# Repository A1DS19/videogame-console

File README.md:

# RP2350 Videogame Console

A homebrew videogame console built around the Raspberry Pi **RP2350B**, with a matching
8-button arcade controller. Both PCBs are designed circuit-as-code (JITX) and taken through
KiCad layout → Freerouting → DRC → JLCPCB fabrication.

| Console | Controller |
|---|---|
|  |  |

## The console

The main board: an RP2350B microcontroller that reads up to two controllers, renders to a TV
over HDMI/DVI, and plays game audio through a small speaker.

- **MCU:** RP2350B (QFN-80) + 16 MB QSPI flash (W25Q128JV), 12 MHz crystal
- **Video:** HDMI connector driven as DVI over the RP2350 HSTX peripheral (4 TMDS pairs)
- **Power:** USB-C in → 3.3 V buck (TLV62569) + the RP2350 core SMPS
- **Controllers:** 2× JST-XH 1×10 ports (one per controller), each with SRV05-4A ESD
- **Audio:** PWM → RC filter → PAM8302A class-D amp → JST-PH speaker
- **I/O:** BOOTSEL + RUN buttons, status LED
- **Board:** 72 × 66 mm, 4-layer (JLC04161H), 75 parts

## The controller

An 8-button arcade-style gamepad on a single faceplate PCB that plugs into a console port
with a JST-XH cable.

- **Buttons:** 8 tactile switches (active-low; pull-ups + 3V3 live on the console end)
- **Link:** JST-XH 1×10 (8 buttons + GND + 3V3)
- **Protection:** SRV05-4A ESD arrays on the button lines
- **Board:** 120 × 70 mm, 2-layer, 31 parts

## Layout

```
pcbs/
  console/        RP2350 console — JITX source, KiCad export, routed board, fab
    routing/production/   JLCPCB gerbers + drill + CPL + BOM
  controller/     arcade gamepad — JITX source, routed board, fab
    fab/                  JLCPCB gerbers + drill + CPL + BOM + STEP
  screenshots/    3D renders
```

Each board's `routing/` holds the canonical routed `.kicad_pcb`. The JLCPCB upload set
(gerbers zip, drill, CPL/position CSV, and an LCSC-resolved BOM) lives in the console's
`routing/production/` and the controller's `fab/`.

## Manufacturing status

- **Console** — fully routed + **DRC clean** (0 unconnected; only the benign `J1` USB-C shield
  annular). Datasheet-validation fixes applied (81 parts). Fab package in
  `routing/production-v2/` (gerbers + drill + CPL + STEP + JLCPCB-uploadable BOM, gate PASS).
- **Controller** — fully routed, DRC clean, fab package ready.

## Rebuilding from source

Each project is a JITX (Python) design. Recreate its virtualenv in the project folder
(`.venv` is not committed and is path-specific), then build with the project `.venv/bin/jitx`.
The routed boards are committed because they are not regenerable from source (Freerouting +
manual finishing) — do not re-export over them.

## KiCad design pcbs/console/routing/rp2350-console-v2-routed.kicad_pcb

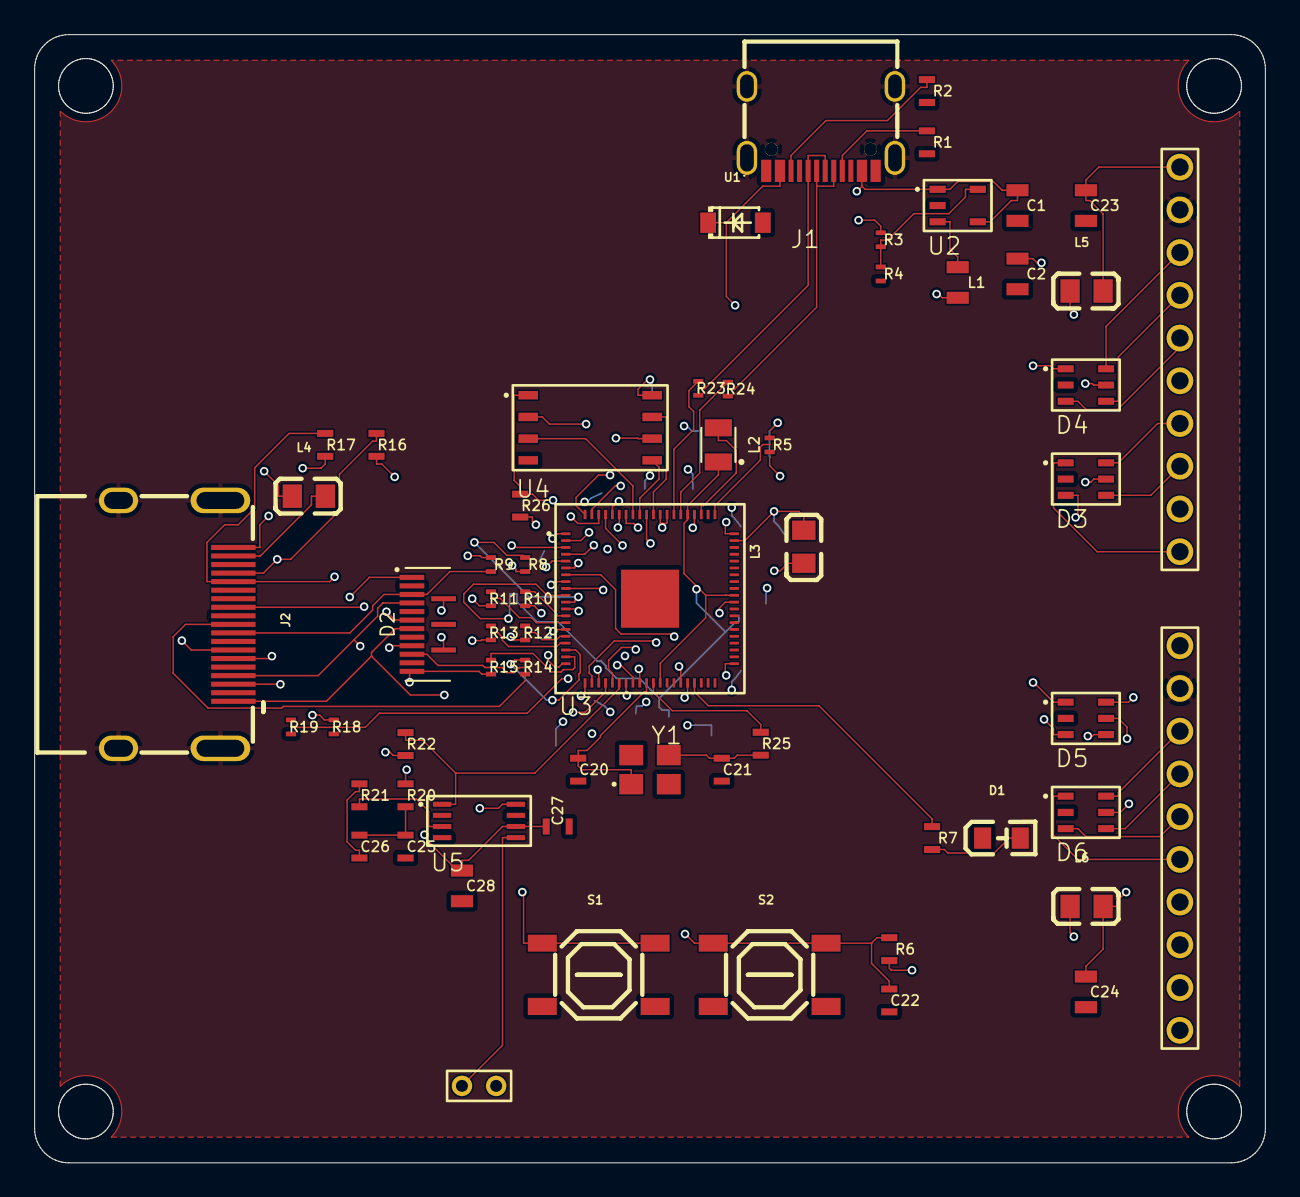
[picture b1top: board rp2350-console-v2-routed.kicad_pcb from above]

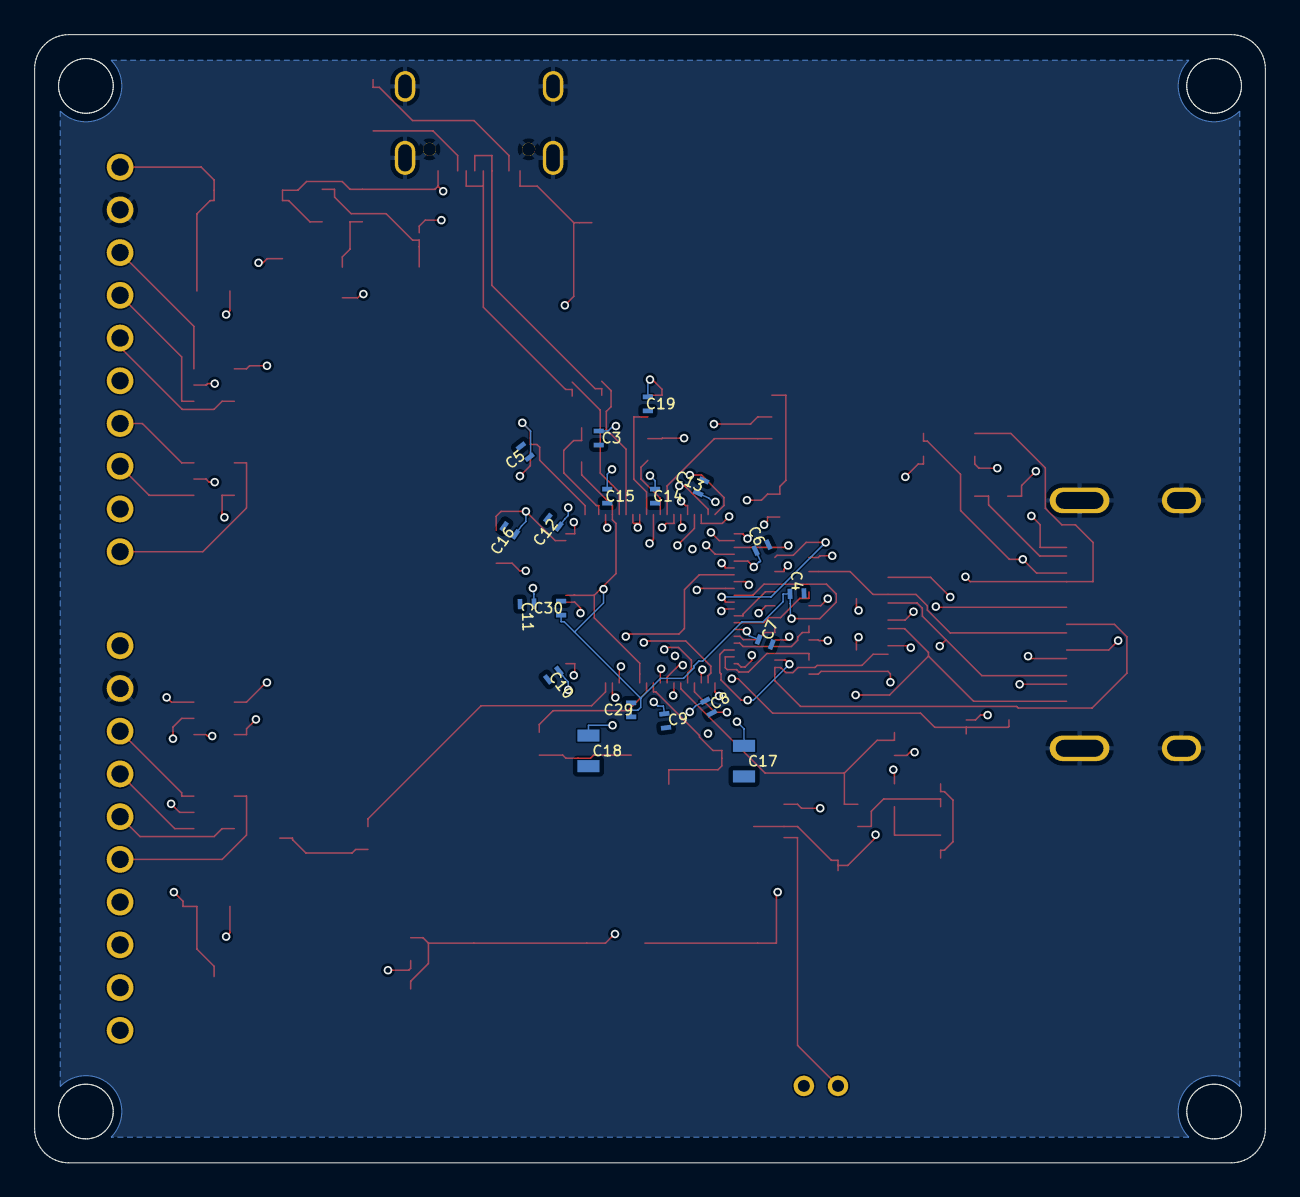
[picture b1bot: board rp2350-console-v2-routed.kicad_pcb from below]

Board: 4 copper layers, 72.0 x 66.0 mm, 81 parts (19 on the bottom side), 74 nets.

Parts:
C1: 10 µF; DBLANDPATTERN_10
C2: 22 µF; DBLANDPATTERN_11
C3: 4.7 µF; DBLANDPATTERN_14
C4: 4.7 µF; DBLANDPATTERN_15
C5: 4.7 µF; DBLANDPATTERN_19
C6: 100 nF; DBLANDPATTERN_20
C7: 100 nF; DBLANDPATTERN_21
C8: 100 nF; DBLANDPATTERN_22
C9: 100 nF; DBLANDPATTERN_23
C10: 100 nF; DBLANDPATTERN_24
C11: 100 nF; DBLANDPATTERN_25
C12: 100 nF; DBLANDPATTERN_26
C13: 100 nF; DBLANDPATTERN_27
C14: 100 nF; DBLANDPATTERN_28
C15: 100 nF; DBLANDPATTERN_29
C16: 100 nF; DBLANDPATTERN_30
C17: 10 µF; DBLANDPATTERN_31
C18: 10 µF; DBLANDPATTERN_32
C19: 100 nF; DBLANDPATTERN_33
C20: 30 pF; DBLANDPATTERN_35
C21: 30 pF; DBLANDPATTERN_36
C22: 100 nF; DBLANDPATTERN_39
C23: 10 µF; DBLANDPATTERN_57
C24: 10 µF; DBLANDPATTERN_58
C25: 2.2 nF; DBLANDPATTERN_60
C26: 1 µF; DBLANDPATTERN_62
C27: 1 µF; DBLANDPATTERN_64
C28: 10 µF; DBLANDPATTERN_65
C29: 100 nF; DBLANDPATTERN_16
C30: 100 nF; DBLANDPATTERN_17
D1: KT-0805G; DBLANDPATTERN_4
D2: TPD8S009DSMR; TPD8S009_COMPOSITE_LANDPATTERN
D3: SRV05-4A; SRV05_4A_COMPOSITE_LANDPATTERN
D4: SRV05-4A; SRV05_4A_COMPOSITE_LANDPATTERN_1
D5: SRV05-4A; SRV05_4A_COMPOSITE_LANDPATTERN_2
D6: SRV05-4A; SRV05_4A_COMPOSITE_LANDPATTERN_3
J1: TYPE-C-31-M-12; Pkg_TYPEC31M12LANDPATTERN
J2: HDMI-001S; DBLANDPATTERN_41
J3: B10B-XH-A(LF)(SN); JSTXH10_COMPOSITE_LANDPATTERN
J4: B10B-XH-A(LF)(SN); JSTXH10_COMPOSITE_LANDPATTERN_1
J5: B2B-PH-K-S(LF)(SN); JSTPH2_COMPOSITE_LANDPATTERN
L1: 2.2 µH; DBLANDPATTERN_1
L2: AOTA-B201610S3R3-101-T; AOTAB201610S3R3_COMPOSITE_LANDPATTERN
L3: GZ2012D101TF; DBLANDPATTERN_5
L4: GZ2012D601TF; DBLANDPATTERN_42
L5: GZ2012D601TF; DBLANDPATTERN_55
L6: GZ2012D601TF; DBLANDPATTERN_56
R1: 5.1 kΩ; DBLANDPATTERN_6
R2: 5.1 kΩ; DBLANDPATTERN_7
R3: 51.7 kΩ; DBLANDPATTERN_12
R4: 11.5 kΩ; DBLANDPATTERN_13
R5: 33 Ω; DBLANDPATTERN_18
R6: 10 kΩ; DBLANDPATTERN_38
R7: 1 kΩ; DBLANDPATTERN_40
R8: 0 Ω; DBLANDPATTERN_43
R9: 0 Ω; DBLANDPATTERN_44
R10: 0 Ω; DBLANDPATTERN_45
R11: 0 Ω; DBLANDPATTERN_46
R12: 0 Ω; DBLANDPATTERN_47
R13: 0 Ω; DBLANDPATTERN_48
R14: 0 Ω; DBLANDPATTERN_49
R15: 0 Ω; DBLANDPATTERN_50
R16: 4.7 kΩ; DBLANDPATTERN_51
R17: 4.7 kΩ; DBLANDPATTERN_52
R18: 110 kΩ; DBLANDPATTERN_53
R19: 165 kΩ; DBLANDPATTERN_54
R20: 3.3 kΩ; DBLANDPATTERN_59
R21: 0 Ω; DBLANDPATTERN_61
R22: 100 kΩ; DBLANDPATTERN_63
R23: 27 Ω; DBLANDPATTERN_8
R24: 27 Ω; DBLANDPATTERN_9
R25: 1 kΩ; DBLANDPATTERN_34
R26: 1 kΩ; DBLANDPATTERN_37
S1: TS-1187A-B-A-B; DBLANDPATTERN_2
S2: TS-1187A-B-A-B; DBLANDPATTERN_3
U1: SMF5.0A; DBLANDPATTERN
U2: TLV62569DBVR; TLV62569_COMPOSITE_LANDPATTERN
U3: RP2350B; RP2350B_COMPOSITE_LANDPATTERN
U4: W25Q128JVSIQ; W25Q128JV_COMPOSITE_LANDPATTERN
U5: PAM8302AASCR; PAM8302A_COMPOSITE_LANDPATTERN
Y1: X322512MSB4SI; CRYSTAL12MHZ_COMPOSITE_LANDPATTERN

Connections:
A: R26.2, S1.1, S1.2
ADC_AVDD: C16.1, L3.2, U3.landpattern_p59
AMP_SD: R22.1, U3.landpattern_p26, U5.landpattern_p1
D0_N: D2.landpattern_p3, J2.9, R9.2
D0_P: D2.landpattern_p1, J2.7, R8.2
D1_N: D2.landpattern_p6, J2.6, R11.2
D1_P: D2.landpattern_p4, J2.4, R10.2
D2_N: D2.landpattern_p9, J2.3, R13.2
D2_P: D2.landpattern_p7, J2.1, R12.2
D3_N: D2.landpattern_p12, J2.12, R15.2
D3_P: D2.landpattern_p10, J2.10, R14.2
DVDD: C4.1, C29.1, C30.1, L2.landpattern_p1, U3.landpattern_p10, U3.landpattern_p32, U3.landpattern_p51, U3.landpattern_p65
FB: R3.2, R4.1, U2.landpattern_p5
GND: C1.2, C2.2, C3.2, C4.2, C5.2, C6.2, C7.2, C8.2, C9.2, C10.2, C11.2, C12.2, C13.2, C14.2, C15.2, C16.2, C17.2, C18.2, C19.2, C20.2, C21.2, C22.2, C23.2, C24.2, C25.2, C27.2, C28.2, C29.2, C30.2, D1.1, D2.landpattern_p2, D2.landpattern_p5, D2.landpattern_p8, D2.landpattern_p11, D3.landpattern_p2, D4.landpattern_p2, D5.landpattern_p2, D6.landpattern_p2, J1.9, J1.10, J1.13, J1.14, J1.15, J1.16, J1.17, J1.18, J2.2, J2.5, J2.8, J2.11, J2.17, J2.20, J2.21, J2.22, J2.23, J3.landpattern_p9, J4.landpattern_p9, R1.2, R2.2, R4.2, R19.2, S1.3, S1.4, S2.3, S2.4, U1.2, U2.landpattern_p2, U3.landpattern_p62, U3.landpattern_thermal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, U4.landpattern_p4, U5.landpattern_p4, U5.landpattern_p7, Y1.landpattern_p2, Y1.landpattern_p4
GPIO[0]: D3.landpattern_p1, J3.landpattern_p1, U3.landpattern_p77
GPIO[1]: D3.landpattern_p3, J3.landpattern_p2, U3.landpattern_p78
GPIO[2]: D3.landpattern_p4, J3.landpattern_p3, U3.landpattern_p79
GPIO[3]: D3.landpattern_p6, J3.landpattern_p4, U3.landpattern_p80
GPIO[4]: D4.landpattern_p1, J3.landpattern_p5, U3.landpattern_p1
GPIO[5]: D4.landpattern_p3, J3.landpattern_p6, U3.landpattern_p2
GPIO[6]: D4.landpattern_p4, J3.landpattern_p7, U3.landpattern_p3
GPIO[7]: D4.landpattern_p6, J3.landpattern_p8, U3.landpattern_p4
GPIO[8]: D5.landpattern_p1, J4.landpattern_p1, U3.landpattern_p6
GPIO[9]: D5.landpattern_p3, J4.landpattern_p2, U3.landpattern_p7
GPIO[10]: D5.landpattern_p4, J4.landpattern_p3, U3.landpattern_p8
GPIO[11]: D5.landpattern_p6, J4.landpattern_p4, U3.landpattern_p9
GPIO[12]: R8.1, U3.landpattern_p11
GPIO[13]: R9.1, U3.landpattern_p12
GPIO[14]: R10.1, U3.landpattern_p13
GPIO[15]: R11.1, U3.landpattern_p14
GPIO[16]: R12.1, U3.landpattern_p16
GPIO[17]: R13.1, U3.landpattern_p17
GPIO[18]: R14.1, U3.landpattern_p18
GPIO[19]: R15.1, U3.landpattern_p19
GPIO[20]: D6.landpattern_p1, J4.landpattern_p5, U3.landpattern_p20
GPIO[21]: D6.landpattern_p3, J4.landpattern_p6, U3.landpattern_p21
GPIO[22]: D6.landpattern_p4, J4.landpattern_p7, U3.landpattern_p22
GPIO[23]: D6.landpattern_p6, J4.landpattern_p8, U3.landpattern_p23
GPIO[24]: R20.1, U3.landpattern_p25
GPIO[26]: J2.16, R16.1, U3.landpattern_p27
GPIO[27]: J2.15, R17.1, U3.landpattern_p28
GPIO[28]: R18.2, R19.1, U3.landpattern_p36
GPIO[29]: R7.1, U3.landpattern_p37
INP: R21.2, U5.landpattern_p3
LED_A: D1.2, R7.2
OUTN: J5.landpattern_p2, U5.landpattern_p8
OUTP: J5.landpattern_p1, U5.landpattern_p5
QSPI_SCLK: U3.landpattern_p71, U4.landpattern_p6
QSPI_SD0: U3.landpattern_p72, U4.landpattern_p5
QSPI_SD1: U3.landpattern_p74, U4.landpattern_p2
QSPI_SD2: U3.landpattern_p73, U4.landpattern_p3
QSPI_SD3: U3.landpattern_p70, U4.landpattern_p7
QSPI_SS: R26.1, U3.landpattern_p75, U4.landpattern_p1
RUN: C22.1, R6.1, S2.1, S2.2, U3.landpattern_p35
SW: L1.1, U2.landpattern_p3
USB_DM: R24.1, U3.landpattern_p66
USB_DP: R23.1, U3.landpattern_p67
V3V3: C2.1, C3.1, C6.1, C7.1, C8.1, C9.1, C10.1, C11.1, C12.1, C13.1, C14.1, C15.1, C17.1, C18.1, C19.1, D2.landpattern_p13, D2.landpattern_p15, D3.landpattern_p5, D4.landpattern_p5, D5.landpattern_p5, D6.landpattern_p5, L1.2, L3.1, L5.1, L6.1, R3.1, R5.2, R6.2, R16.2, R17.2, R22.2, U3.landpattern_p5, U3.landpattern_p15, U3.landpattern_p24, U3.landpattern_p29, U3.landpattern_p41, U3.landpattern_p50, U3.landpattern_p60, U3.landpattern_p64, U3.landpattern_p68, U3.landpattern_p69, U3.landpattern_p76, U4.landpattern_p8
VBUS: C1.1, C27.1, C28.1, J1.11, J1.12, L4.1, U1.1, U2.landpattern_p1, U2.landpattern_p4, U5.landpattern_p6
VREG_AVDD: C5.1, R5.1, U3.landpattern_p61
VREG_LX: L2.landpattern_p2, U3.landpattern_p63
XIN: C20.1, U3.landpattern_p30, Y1.landpattern_p1
XOUT: R25.1, U3.landpattern_p31
c_ac_p1: C25.1, C26.1, R20.2
c_port_bulk[0]_p1: C23.1, J3.landpattern_p10, L5.2
c_port_bulk[1]_p1: C24.1, J4.landpattern_p10, L6.2
p1: J1.2, R1.1
p2: C26.2, R21.1
p[2]: J2.18, L4.2
r_cc2_p1: J1.8, R2.1
r_hi_p1: J2.19, R18.1
r_usb_dm_p2: J1.3, J1.5, R24.2
r_usb_dp_p2: J1.4, J1.6, R23.2
xtal_XOUT: C21.1, R25.2, Y1.landpattern_p3

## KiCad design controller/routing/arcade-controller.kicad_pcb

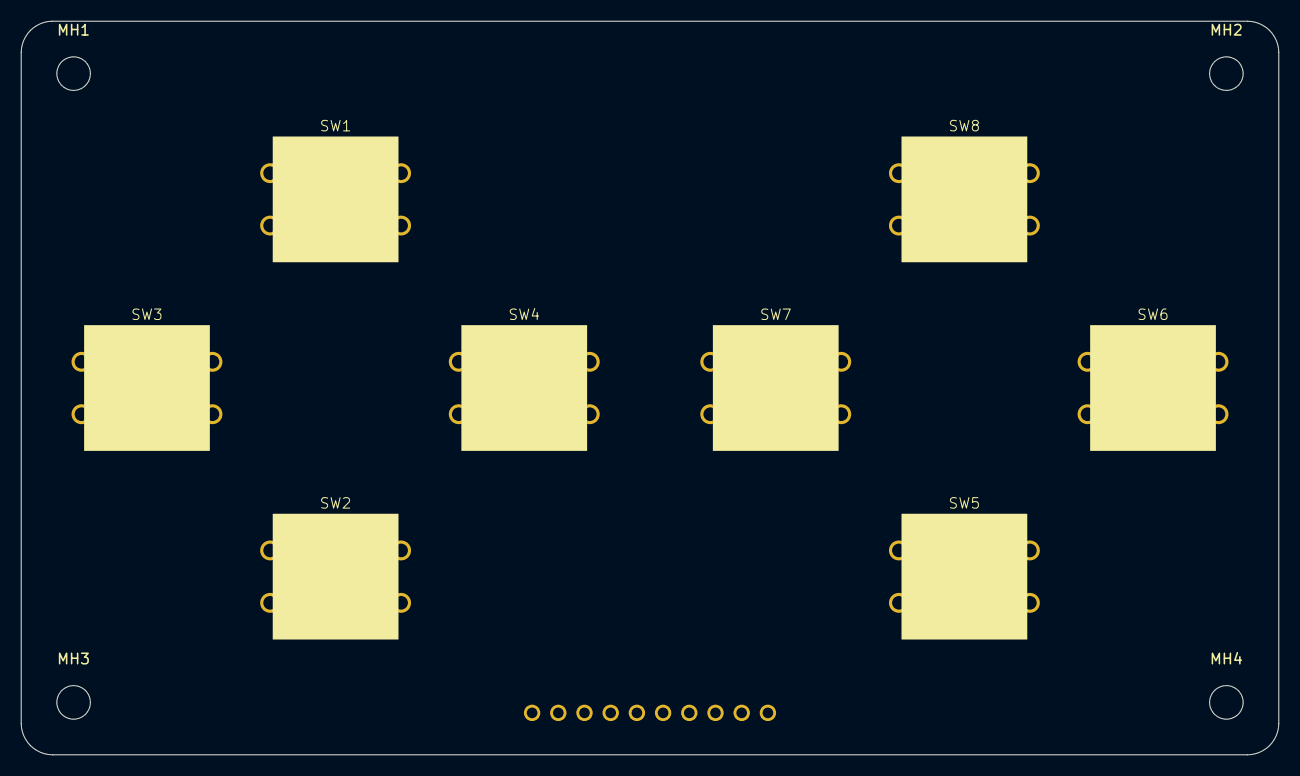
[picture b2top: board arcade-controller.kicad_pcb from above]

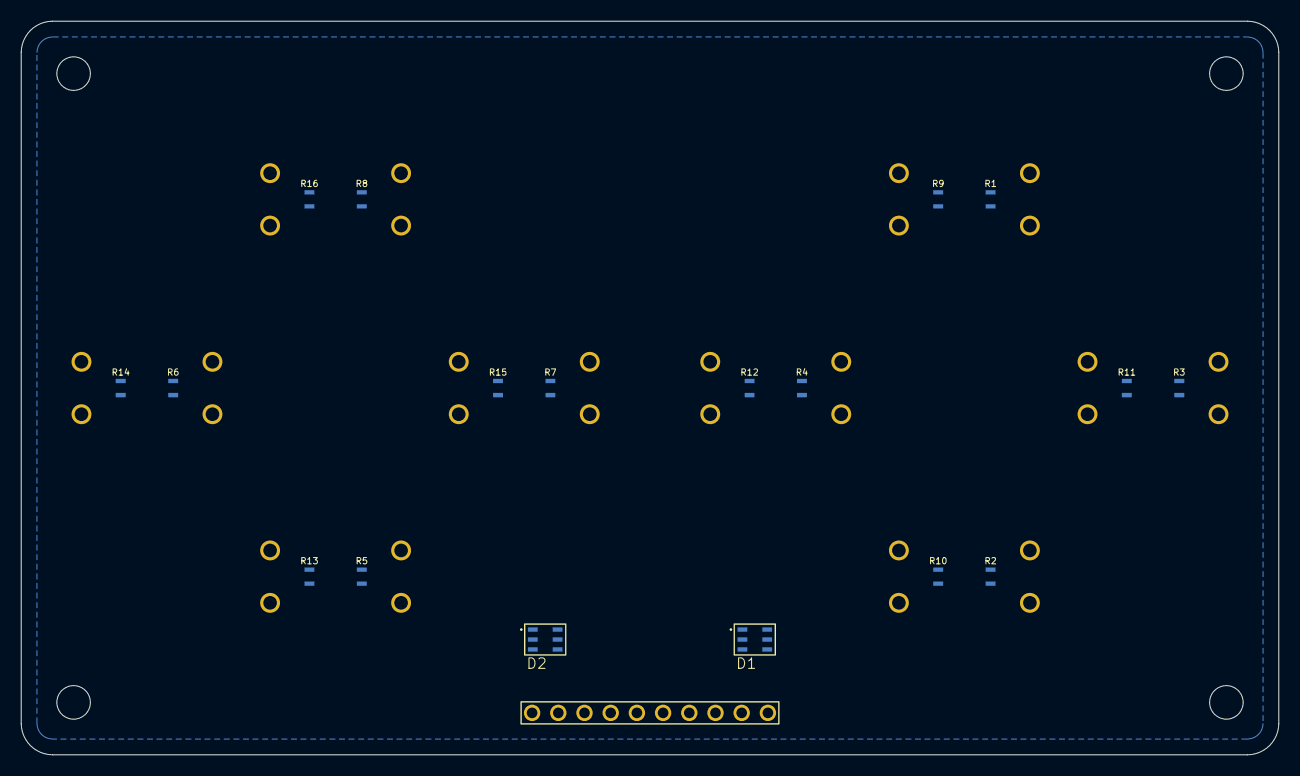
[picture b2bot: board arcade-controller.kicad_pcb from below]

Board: 2 copper layers, 120.0 x 70.0 mm, 31 parts (19 on the bottom side), 18 nets, no tracks yet.

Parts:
D1: SRV05-4A; SRV05_4A_COMPOSITE_LANDPATTERN
D2: SRV05-4A; SRV05_4A_COMPOSITE_LANDPATTERN_1
J1: B10B-XH-A(LF)(SN); JSTXH10_COMPOSITE_LANDPATTERN
MH1, MH2, MH3, MH4: MountingHole_3.2mm_M3
R1: 10 kΩ; DBLANDPATTERN
R2: 10 kΩ; DBLANDPATTERN_1
R3: 10 kΩ; DBLANDPATTERN_2
R4: 10 kΩ; DBLANDPATTERN_3
R5: 10 kΩ; DBLANDPATTERN_4
R6: 10 kΩ; DBLANDPATTERN_5
R7: 10 kΩ; DBLANDPATTERN_6
R8: 10 kΩ; DBLANDPATTERN_7
R9: 220 Ω; DBLANDPATTERN_8
R10: 220 Ω; DBLANDPATTERN_9
R11: 220 Ω; DBLANDPATTERN_10
R12: 220 Ω; DBLANDPATTERN_11
R13: 220 Ω; DBLANDPATTERN_12
R14: 220 Ω; DBLANDPATTERN_13
R15: 220 Ω; DBLANDPATTERN_14
R16: 220 Ω; DBLANDPATTERN_15
SW1, SW2, SW3, SW4, SW5, SW6, SW7, SW8: K2-1103DP-Q4SW-04; Pkg_TACTILEBUTTONLANDPATTERN

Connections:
BTN0_INT: R1.2, R9.1, SW1.1, SW1.2
BTN0_OUT: D1.landpattern_p1, J1.landpattern_p1, R9.2
BTN1_INT: R2.2, R10.1, SW2.1, SW2.2
BTN1_OUT: D1.landpattern_p3, J1.landpattern_p2, R10.2
BTN2_INT: R3.2, R11.1, SW3.1, SW3.2
BTN2_OUT: D1.landpattern_p4, J1.landpattern_p3, R11.2
BTN3_INT: R4.2, R12.1, SW4.1, SW4.2
BTN3_OUT: D1.landpattern_p6, J1.landpattern_p4, R12.2
BTN4_INT: R5.2, R13.1, SW5.1, SW5.2
BTN4_OUT: D2.landpattern_p1, J1.landpattern_p5, R13.2
BTN5_INT: R6.2, R14.1, SW6.1, SW6.2
BTN5_OUT: D2.landpattern_p3, J1.landpattern_p6, R14.2
BTN6_INT: R7.2, R15.1, SW7.1, SW7.2
BTN6_OUT: D2.landpattern_p4, J1.landpattern_p7, R15.2
BTN7_INT: R8.2, R16.1, SW8.1, SW8.2
BTN7_OUT: D2.landpattern_p6, J1.landpattern_p8, R16.2
GND: D1.landpattern_p2, D2.landpattern_p2, J1.landpattern_p9, SW1.3, SW1.4, SW2.3, SW2.4, SW3.3, SW3.4, SW4.3, SW4.4, SW5.3, SW5.4, SW6.3, SW6.4, SW7.3, SW7.4, SW8.3, SW8.4
V3V3: D1.landpattern_p5, D2.landpattern_p5, J1.landpattern_p10, R1.1, R2.1, R3.1, R4.1, R5.1, R6.1, R7.1, R8.1

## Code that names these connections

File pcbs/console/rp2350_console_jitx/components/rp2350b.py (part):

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  • GPIO40–GPIO47 carry the 8 ADC inputs (ADC0–ADC7) on QFN-80 (Table 1119).
  • GPIO0–GPIO47 (48 pins) is the full bank used for the 2 controller ports,
    PWM audio, status LED, and DDC/HPD — exposed here as the GPIO[0..47] list.
  • QSPI_SS (pin 75) doubles as the USB BOOTSEL strap (Table 1428).
  • GND has no dedicated pin — it is the central exposed pad only (Table 1432).
"""

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        for i, pad in enumerate(_IOVDD_PADS):
            mapping[self.IOVDD[i]] = [lp.p[pad]]
        for i, pad in enumerate(_DVDD_PADS):
            mapping[self.DVDD[i]] = [lp.p[pad]]
        mapping[self.ADC_AVDD] = [lp.p[59]]
        mapping[self.VREG_AVDD] = [lp.p[61]]
        mapping[self.VREG_PGND] = [lp.p[62]]
        mapping[self.VREG_LX] = [lp.p[63]]
        mapping[self.VREG_VIN] = [lp.p[64]]
        mapping[self.VREG_FB] = [lp.p[65]]
        mapping[self.USB_DM] = [lp.p[66]]
        mapping[self.USB_DP] = [lp.p[67]]
        mapping[self.USB_OTP_VDD] = [lp.p[68]]
        mapping[self.QSPI_IOVDD] = [lp.p[69]]
        mapping[self.QSPI_SD3] = [lp.p[70]]
        mapping[self.QSPI_SCLK] = [lp.p[71]]
        mapping[self.QSPI_SD0] = [lp.p[72]]
        mapping[self.QSPI_SD2] = [lp.p[73]]
        mapping[self.QSPI_SD1] = [lp.p[74]]
        mapping[self.QSPI_SS] = [lp.p[75]]
        mapping[self.XIN] = [lp.p[30]]
        mapping[self.XOUT] = [lp.p[31]]
        mapping[self.SWCLK] = [lp.p[33]]
        mapping[self.SWDIO] = [lp.p[34]]
        mapping[self.RUN] = [lp.p[35]]
        mapping[self.GND] = [lp.thermal_pads[0]]

        self.mappings = [PadMapping(mapping)]
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
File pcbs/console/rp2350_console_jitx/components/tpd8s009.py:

"""
Texas Instruments TPD8S009DSMR — 8-channel TVS/ESD protection array for
DisplayPort/HDMI/DVI TMDS lines.  LCSC C471873.

Package: DSM (R-PDSO-N15), 15-pin SON, body 6.50 x 2.50 mm
  (datasheet "Package Information" table, p.1: SON(15), 2.50 x 6.50 mm body).

Pinout — datasheet p.3, "Figure 4-1. DSM Package 15-Pin SON Top View" +
"Pin Functions" table:
  Pin  1  D0+   ESD port   (TMDS data 0, +)
  Pin  2  GND   ground
  Pin  3  D0-   ESD port   (TMDS data 0, -)
  Pin  4  D1+   ESD port   (TMDS data 1, +)
  Pin  5  GND   ground
  Pin  6  D1-   ESD port   (TMDS data 1, -)
  Pin  7  D2+   ESD port   (TMDS data 2, +)
  Pin  8  GND   ground
  Pin  9  D2-   ESD port   (TMDS data 2, -)
  Pin 10  D3+   ESD port   (TMDS data 3/clock, +)
  Pin 11  GND   ground
  Pin 12  D3-   ESD port   (TMDS data 3/clock, -)
  Pin 13  VCC   I/O supply
  Pin 14  N.C.  not internally connected
  Pin 15  VCC   I/O supply

Each ESD channel is a single SHUNT node (steering diodes clamp the line to
GND/VCC per the "Simplified Internal Schematic", p.1) — it is NOT a series
pass-through; the "Easy Straight-Through Routing Package" feature is a layout
convenience (pins arranged so the TMDS pairs route straight past with short
stubs), not separate connector-side/MCU-side terminals.

Landpattern — datasheet p.16 "LAND PATTERN" (drawing 4210120/A) + p.15
"MECHANICAL DATA" (DSM R-PDSO-N15, 4208854/A):
  Row A (pins 1-12): one long edge, pitch 0.50 mm, span 5.50 mm.
  Row B (pins 13-15): opposite long edge, pitch 1.50 mm, span 3.00 mm.
  Recommended copper land: 0.30 mm (across) x 1.45 mm (along), non-solder-mask
  defined (0.06 mm mask relief all around), stencil aperture 0.25 x 1.40 mm.
  Row-to-row land centre-to-centre = 3.30 mm overall - 1.45 mm land = 1.85 mm
  => each row centred at Y = +-0.925 mm.
Pad centres cross-checked against the JITX parts-DB landpattern for
TPD8S009DSMR (build --no-dependency-check probe) — identical poses.
No exposed/thermal pad (lead-frame SON, terminals on two opposing edges only).

3D model: manufacturer STEP from the JITX parts DB (resolved via
Part(mpn="TPD8S009DSMR")), vendored to models/TPD8S009DSMR.stp.
"""

import jitx
from jitx import PadMapping
from jitx.anchor import Anchor
from jitx.feature import Courtyard, Custom, Paste, Silkscreen, Soldermask
from jitx.landpattern import Landpattern, Pad
from jitx.model3d import Model3D
from jitx.net import Port
from jitx.shapes.composites import rectangle
from jitx.shapes.primitive import Circle, Polyline, Text
from jitxlib.symbols.box import BoxSymbol, Column, PinGroup, Row


# ======================================================================
# Pad — single SMD land shared by all 15 terminals (datasheet p.16)
# ======================================================================


class _Land(Pad):
    """SMD land 0.30 (across) x 1.45 mm (along), NSMD + stencil aperture."""

    shape = rectangle(0.30, 1.45)
    soldermask = Soldermask(rectangle(0.42, 1.57))  # +0.06 mm relief all around
    paste = Paste(rectangle(0.25, 1.40))  # datasheet stencil aperture


# ======================================================================
# Landpattern (module scope — JITX prohibits subclassing inside __init__)
# ======================================================================


class _Tpd8s009Landpattern(Landpattern):
    """
    R-PDSO-N15 (DSM) land pattern, top (PCB) view.

    Row A (Y = +0.925): pins 1-12 left-to-right at X = +2.75 .. -2.75, 0.50 pitch.
    Row B (Y = -0.925): pins 13/14/15 at X = -1.50 / 0.00 / +1.50, 1.50 pitch.
    Pin 1 (D0+) sits at the +X end of row A (top view).
    """

    name = "TI:R-PDSO-N15_TPD8S009DSM"

    # Row A — pins 1..12 at Y = +0.925, X stepping -0.50 from +2.75.
    # Row B — pins 13..15 at Y = -0.925.
    p = {
        1: _Land().at(2.75, 0.925),
        2: _Land().at(2.25, 0.925),
        3: _Land().at(1.75, 0.925),
        4: _Land().at(1.25, 0.925),
        5: _Land().at(0.75, 0.925),
        6: _Land().at(0.25, 0.925),
        7: _Land().at(-0.25, 0.925),
        8: _Land().at(-0.75, 0.925),
        9: _Land().at(-1.25, 0.925),
        10: _Land().at(-1.75, 0.925),
        11: _Land().at(-2.25, 0.925),
        12: _Land().at(-2.75, 0.925),
        13: _Land().at(-1.50, -0.925),
        14: _Land().at(0.00, -0.925),
        15: _Land().at(1.50, -0.925),
    }

    # Silkscreen: short body-edge lines (clear of the lands) + pin-1 dot.
    # Body 6.60 x 2.60 mm => half-extents X = 3.30, Y = 1.30 (datasheet p.15).
    silkscreen = [
        Silkscreen(Polyline(0.12, [(3.30, -1.30), (3.30, 1.30)])),
        Silkscreen(Polyline(0.12, [(-3.30, -1.30), (-3.30, 1.30)])),
        Silkscreen(Circle(radius=0.15).at((3.20, 1.80))),  # pin-1 marker
    ]
    reference_designator = Silkscreen(Text(">REF", 0.8, Anchor.C).at((0.0, 2.35)))
    value_label = Custom(Text(">VALUE", 0.8, Anchor.C).at((0.0, -2.35)), name="Fab")

    # Courtyard covers the lands (Y +-1.65) and body (X +-3.30) + ~0.25 mm.
    courtyard = Courtyard(rectangle(7.10, 3.80))


# ======================================================================
# Component
# ======================================================================


class Tpd8s009(jitx.Component):
    """TI TPD8S009 8-channel HDMI/DisplayPort TMDS ESD protection array, SON-15."""

    mpn = "TPD8S009DSMR"
    manufacturer = "Texas Instruments"
    lcsc = "C471873"
    reference_designator_prefix = "D"
    datasheet = "https://www.ti.com/lit/ds/symlink/tpd8s009.pdf"

    # 8 high-speed ESD channels = the 4 TMDS differential pairs (pins 1,3,4,6,7,9,10,12)
    D0_P = Port()  # pin 1
    D0_N = Port()  # pin 3
    D1_P = Port()  # pin 4
    D1_N = Port()  # pin 6
    D2_P = Port()  # pin 7
    D2_N = Port()  # pin 9
    D3_P = Port()  # pin 10
    D3_N = Port()  # pin 12

    # Ground returns — pins 2, 5, 8, 11
    GND = [Port() for _ in range(4)]

    # I/O supply rail — pins 13, 15
    VCC = [Port() for _ in range(2)]

    # Not internally connected — pin 14
    NC = Port()

    landpattern = _Tpd8s009Landpattern()

    # Manufacturer STEP (JITX parts DB), vendored to models/.
    # Resolves relative to this file: components/ -> project_root/models/.
    # Origin-centred DB model (position/rotation = 0); HUMAN: confirm seating
    # in the 3D view after export and adjust if needed.
    model3ds = [Model3D("../../models/TPD8S009DSMR.stp")]

    def __init__(self) -> None:
        # Symbol: TMDS channels on the left (pair-ordered), VCC/NC right, GND down.
        self.symbol = BoxSymbol(
            rows=Row(
                left=PinGroup(
                    self.D0_P,
                    self.D0_N,
                    self.D1_P,
                    self.D1_N,
                    self.D2_P,
                    self.D2_N,
                    self.D3_P,
                    self.D3_N,
                ),
                right=PinGroup(*self.VCC, self.NC),
            ),
            columns=Column(
                down=PinGroup(*self.GND),
            ),
        )

        # Port -> pad number per datasheet "Pin Functions" table (p.3).
        lp = self.landpattern
        self.mappings = [
            PadMapping(
                {
                    self.D0_P: lp.p[1],
                    self.GND[0]: lp.p[2],
                    self.D0_N: lp.p[3],
                    self.D1_P: lp.p[4],
                    self.GND[1]: lp.p[5],
                    self.D1_N: lp.p[6],
                    self.D2_P: lp.p[7],
                    self.GND[2]: lp.p[8],
                    self.D2_N: lp.p[9],
                    self.D3_P: lp.p[10],
                    self.GND[3]: lp.p[11],
                    self.D3_N: lp.p[12],
                    self.VCC[0]: lp.p[13],
                    self.NC: lp.p[14],
                    self.VCC[1]: lp.p[15],
                }
            )
        ]


Device: type[Tpd8s009] = Tpd8s009

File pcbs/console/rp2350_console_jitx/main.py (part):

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        # so this insert is plain (the inductor is the switch-node element, not a
        # decoupling cap) — see grep-gate disposition.
        self.l_buck.insert(self.buck.SW, self.V3V3)
        # Output cap pinned across the inductor output (l_buck.p2 = V3V3) and the
        # buck ground return — both Ports, so short_trace keeps it at the output.
        self.c_buck_out = Capacitor(capacitance=22e-6, case="0805")
        self.c_buck_out.insert(self.l_buck.p2, self.buck.GND, short_trace=True)
        # FB divider from constraints (NEVER hand-picked): V3V3 -> FB -> GND.
        # TLV62569 VFB = 0.6 V nominal (datasheet "Feedback regulation voltage":
        # 0.588 / 0.600 / 0.612 V = 0.6 V +/-2%), so v_out = 0.6 V +/-2%.
        self.fb_div = voltage_divider_from_constraints(
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            + self.mcu.DVDD[2]
            + self.mcu.VREG_FB,
        ]
        # C6 (4.7 uF) core-reg input decoupling; C7 (4.7 uF) on DVDD; both pinned.
        self.c6_core_in = Capacitor(capacitance=4.7e-6, case="0402")
        self.c6_core_in.insert(self.mcu.VREG_VIN, self.mcu.VREG_PGND, short_trace=True)
        self.c7_core_out = Capacitor(capacitance=4.7e-6, case="0402")
        self.c7_core_out.insert(self.mcu.DVDD[0], self.mcu.GND, short_trace=True)
        # 2x 100 nF on the inner DVDD pads (DVDD[1]=pad32, DVDD[2]=pad51) close to the
        # pins per datasheet §6.1.3 (C7 4.7 uF above sits on the furthest DVDD pad).
        self.c_dvdd = [Capacitor(capacitance=100e-9, case="0402") for _ in range(2)]
        self.c_dvdd[0].insert(self.mcu.DVDD[1], self.mcu.GND, short_trace=True)
        self.c_dvdd[1].insert(self.mcu.DVDD[2], self.mcu.GND, short_trace=True)
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            self.mcu.QSPI_SD3 + self.flash.IO3_HOLD,
        ]

        # --- 12 MHz crystal + 1k XOUT damping + load caps ---
        # R2 (1k) in series with XOUT: REQUIRED at 3.3 V IOVDD to keep the crystal from
        # being over-driven/damaged (RP2350 HW guide §4 Fig 10). The load cap stays on
        # the crystal side of R2.
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        # --- Status LED on GPIO29 (lit when the GPIO is driven high) ---
        self.LED_A = Net(name="LED_A")  # series-resistor / LED-anode node
        self.r_led = Resistor(resistance=1e3, case="0603")
        self.r_led.insert(self.mcu.GPIO[29], self.LED_A)
        self.led_nets = [
            self.LED_A + self.led_status.A,
            self.GND + self.led_status.K,
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            self.VBUS + self.fb_hdmi5v.p[1],
            self.hdmi.V5 + self.fb_hdmi5v.p[2],
        ]
        # DDC I2C: SDA=GPIO26, SCL=GPIO27, with 4.7 k pull-ups to V3V3.
        self.ddc_nets = [
            self.mcu.GPIO[26] + self.hdmi.SDA,
            self.mcu.GPIO[27] + self.hdmi.SCL,
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            self.r_in.p2 + self.amp.INP,  # gain resistor -> IN+
            self.GND + self.amp.INN,  # single-ended input reference
        ]
        # Amp shutdown (active-low): driven by GPIO25, 100 k pull-up to V3V3
        # -> default HIGH = amp ENABLED at boot (firmware mutes by driving low).
        self.SD = Net(name="AMP_SD")
        self.SD += self.amp.SD + self.mcu.GPIO[25]
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
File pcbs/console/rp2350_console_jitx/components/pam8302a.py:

"""
Diodes PAM8302AASCR — 2.5 W filterless Class-D mono audio amplifier, MSOP-8.

LCSC C113367. Drives the console's 8 Ω speaker (via a JST-PH port).

Pinout (datasheet DS41333 Rev.6 page 1, "Pin Assignments" MSOP-8 Top View) —
verified against the JITX parts-DB pin_properties for C113367:
  Pin 1: SD    (shutdown, ACTIVE-LOW: logic-low = amp off; overbar /SD)
  Pin 2: NC    (no internal connection)
  Pin 3: IN+   (non-inverting audio input)        -> port INP
  Pin 4: IN-   (inverting audio input)            -> port INN
  Pin 5: VO+   (bridge-tied speaker output +)     -> port OUTP
  Pin 6: VDD   (2.0-5.5 V supply)
  Pin 7: GND   (ground)
  Pin 8: VO-   (bridge-tied speaker output -)     -> port OUTN

MSOP-8 mechanical (datasheet page 10, "Package Outline Dimensions", all mm):
  D  (body length):     2.90-3.10
  E1 (body width):      2.90-3.10
  E  (lead span):       4.70-5.10
  e  (pitch):           0.65
  L  (lead foot length):0.40-0.80
  b  (lead width):      0.22-0.38
  A  (overall height):  max 1.10  (A2 body 0.75-0.95)

Closed-loop gain is set externally (datasheet page 7): GV = 20*log(150k/(10k+Rin)) dB
(~23.5 dB max at Rin=0; the old "2x(142k/Rin)" shorthand is wrong — it diverges at
Rin=0). The differential output is filterless and must
NOT be AC-coupled or ground-referenced; route VO+/VO- straight to the speaker.
"""

import jitx
from jitx import PadMapping
from jitx.model3d import Model3D
from jitx.net import Port
from jitx.toleranced import Toleranced
from jitxlib.landpatterns.generators.sop import SOP, SOPLead
from jitxlib.landpatterns.leads import LeadProfile
from jitxlib.landpatterns.package import RectanglePackage
from jitxlib.symbols.box import BoxSymbol, Column, PinGroup, Row


class PAM8302A(jitx.Component):
    """2.5 W Class-D mono audio amplifier, MSOP-8 (Diodes PAM8302AASCR)."""

    mpn = "PAM8302AASCR"
    manufacturer = "Diodes Incorporated"
    lcsc = "C113367"
    reference_designator_prefix = "U"
    datasheet = "https://www.diodes.com/assets/Datasheets/PAM8302A.pdf"

    # Ports — one per physical pin, named per datasheet page-1 Pin Assignments.
    SD = Port()  # pin 1 — shutdown, active-low (low = amp off)
    NC = Port()  # pin 2 — no connection
    INP = Port()  # pin 3 — IN+ non-inverting input
    INN = Port()  # pin 4 — IN- inverting input
    OUTP = Port()  # pin 5 — VO+ speaker output (+)
    VDD = Port()  # pin 6 — supply 2.0-5.5 V
    GND = Port()  # pin 7 — ground
    OUTN = Port()  # pin 8 — VO- speaker output (-)

    # MSOP-8 landpattern via the SOP generator (gull-wing, 0.65 mm pitch).
    # Dimensions are the datasheet page-10 mechanical drawing (see module docstring).
    landpattern = (
        SOP(num_leads=8)
        .lead_profile(
            LeadProfile(
                span=Toleranced.min_max(4.70, 5.10),  # E — lead tip-to-tip
                pitch=0.65,  # e
                type=SOPLead(
                    length=Toleranced.min_max(0.40, 0.80),  # L — foot length
                    width=Toleranced.min_max(0.22, 0.38),  # b — lead width
                ),
            )
        )
        .package_body(
            RectanglePackage(
                width=Toleranced.min_max(2.90, 3.10),  # E1 — body width
                length=Toleranced.min_max(2.90, 3.10),  # D — body length
                height=Toleranced.min_max(0.86, 1.10),  # A2..A
            )
        )
    )

    # BoxSymbol: inputs + shutdown on the left, speaker outputs on the right,
    # VDD up / GND down — mirrors the datasheet pin directions.
    symbol = BoxSymbol(
        rows=Row(
            left=PinGroup(SD, NC, INP, INN),
            right=PinGroup(OUTP, OUTN),
        ),
        columns=Column(
            up=PinGroup(VDD),
            down=PinGroup(GND),
        ),
    )

    # 3D model: the exact PAM8302AASCR (LCSC C113367) STEP from the JITX parts DB,
    # auto-downloaded to 3d-models/ during the DB probe and copied to models/ with a
    # clean name. The generator landpattern carries no DB 3D automatically, so attach
    # it here to complete the board STEP export. Resolves relative to this file:
    # components/ -> project_root/models/.
    # The DB tags this model "unknown transformation coordinates - please validate
    # before use" (HUMAN: confirm seating in the 3D view after export; adjust
    # offset/rotation if it does not sit flat on the MSOP-8 footprint).
    model3ds = [Model3D("../../models/PAM8302AASCR.stp")]

    # Explicit PadMapping — SOP LinearNumbering pads p[1]..p[8] map to the
    # datasheet pin numbers (left col 1-4 top->bottom, right col 5-8 bottom->top).
    def __init__(self) -> None:
        lp = self.landpattern
        self.mappings = [
            PadMapping(
                {
                    self.SD: [lp.p[1]],
                    self.NC: [lp.p[2]],
                    self.INP: [lp.p[3]],
                    self.INN: [lp.p[4]],
                    self.OUTP: [lp.p[5]],
                    self.VDD: [lp.p[6]],
                    self.GND: [lp.p[7]],
                    self.OUTN: [lp.p[8]],
                }
            )
        ]


Device: type[PAM8302A] = PAM8302A

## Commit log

2026-06-27 Initial: RP2350 videogame console — console + controller
    Consolidated from medi-pal/pcbs into a standalone project:
    console/ RP2350B HDMI/DVI console (routed, 0 unconnected, JLCPCB fab in
    routing/production; 1 hole_to_hole needs a GUI via-shove)
    controller/ 8-button arcade gamepad (routed 0/0/0, JLCPCB fab in fab/)
    Build artifacts (.venv, designs/, 3d-models/) excluded — recreate .venv per project.
2026-06-27 fix(console): JLCPCB-compliant BOM (LCSC + real footprints)
    The raw Fabrication-Toolkit BOM had blank LCSC codes and DBLANDPATTERN footprint
    names -> JLCPCB PCBA would suspend the order. Regenerated via check_bom.py --fix
    (parts-db + 5 manual LCSC for DB-unindexed parts: RP2350B C42415655, USB-C
    C165948, SRV05-4A C20615829, JST-XH C144400, AOTA inductor C42411119). Now
    Comment/Designator/Footprint/LCSC, 75/75 designators, gate PASS. Raw FT BOM kept
    as bom-fabricationtoolkit-raw.csv; LCSC overrides in lcsc-manual.csv.
2026-06-27 chore(console): align BOM format with controller (add Qty column)
    Both boards now: Comment,Designator,Footprint,Qty,LCSC Part #. Regenerated via
    the upgraded check_bom.py --from-sch one-shot.
2026-06-27 chore(console): sync gnd_vias/fix_drc with the pcb-route skill (bug fixes)
    Pick up the hole_to_hole 'no self in Geom' fix (was able to stack same-net vias)
    and seg_seg crossing detection now that these tools are first-class skill scripts.
2026-06-28 docs: add project README with board overviews + 3D renders
2026-06-28 docs
2026-06-29 fix(console): add omitted RP2350 reference parts + correct L1 polarity
    Validation against the RP2350 datasheets surfaced reference-design parts the
    netlist was missing (all DRC-invisible) and one reversed component:
    - USB D+/D-: add the required 27R series termination (R7/R8) — the RP2350 PHY
    integrates pull-ups/downs but NOT series termination (HW guide §5.1)
    - XOSC: add the 1k XOUT damping resistor required at 3.3V IOVDD (§4 Fig 10) and
    pin C0G on the load caps so temperature/bias drift can't pull the oscillator
2026-06-29 chore(console): re-route corrected netlist to GUI-finish state
    The 81-part corrected board (datasheet-validation fixes) re-exported and taken
    through the headless pcb-route flow: the 6 new parts placed (placement gate
    clean; positions back-ported to placement.py), Freerouting @0.2mm clearance,
    then GND/V3V3 plane-tie + grid stitching.
    All signal nets route; remaining DRC = 19 GND/V3V3 plane-tie unconnected + 1
    clearance + 2 benign J1 annular — boxed-in pads (HDMI/ESD fanout, MCU EP) plus
2026-06-29 feat(console): final routed board + JLCPCB fab package (v2)
    GUI finishing complete (GND/V3V3 ties, V3V3 zone island, last via clearance)
    on the corrected 81-part board. DRC clean: 0 unconnected, only the 2 benign
    J1 USB-C shield annular (footprint-baked, allowlisted).
    Fab package routing/production-v2/ (gerbers zip + drill + CPL + STEP + BOM).
    BOM gated PASS: 40 grouped lines / 81 parts, all real packages + LCSC. New
    parts resolved — 27R USB (C2096044), 1k (C2889391), 100nF (C1853702); SMF5.0A
2026-06-29 chore(console): track uv.lock for reproducible builds
